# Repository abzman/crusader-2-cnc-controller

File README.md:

# crusader-2-cnc-controller
boards and roms for the crusader 2 cnc controller

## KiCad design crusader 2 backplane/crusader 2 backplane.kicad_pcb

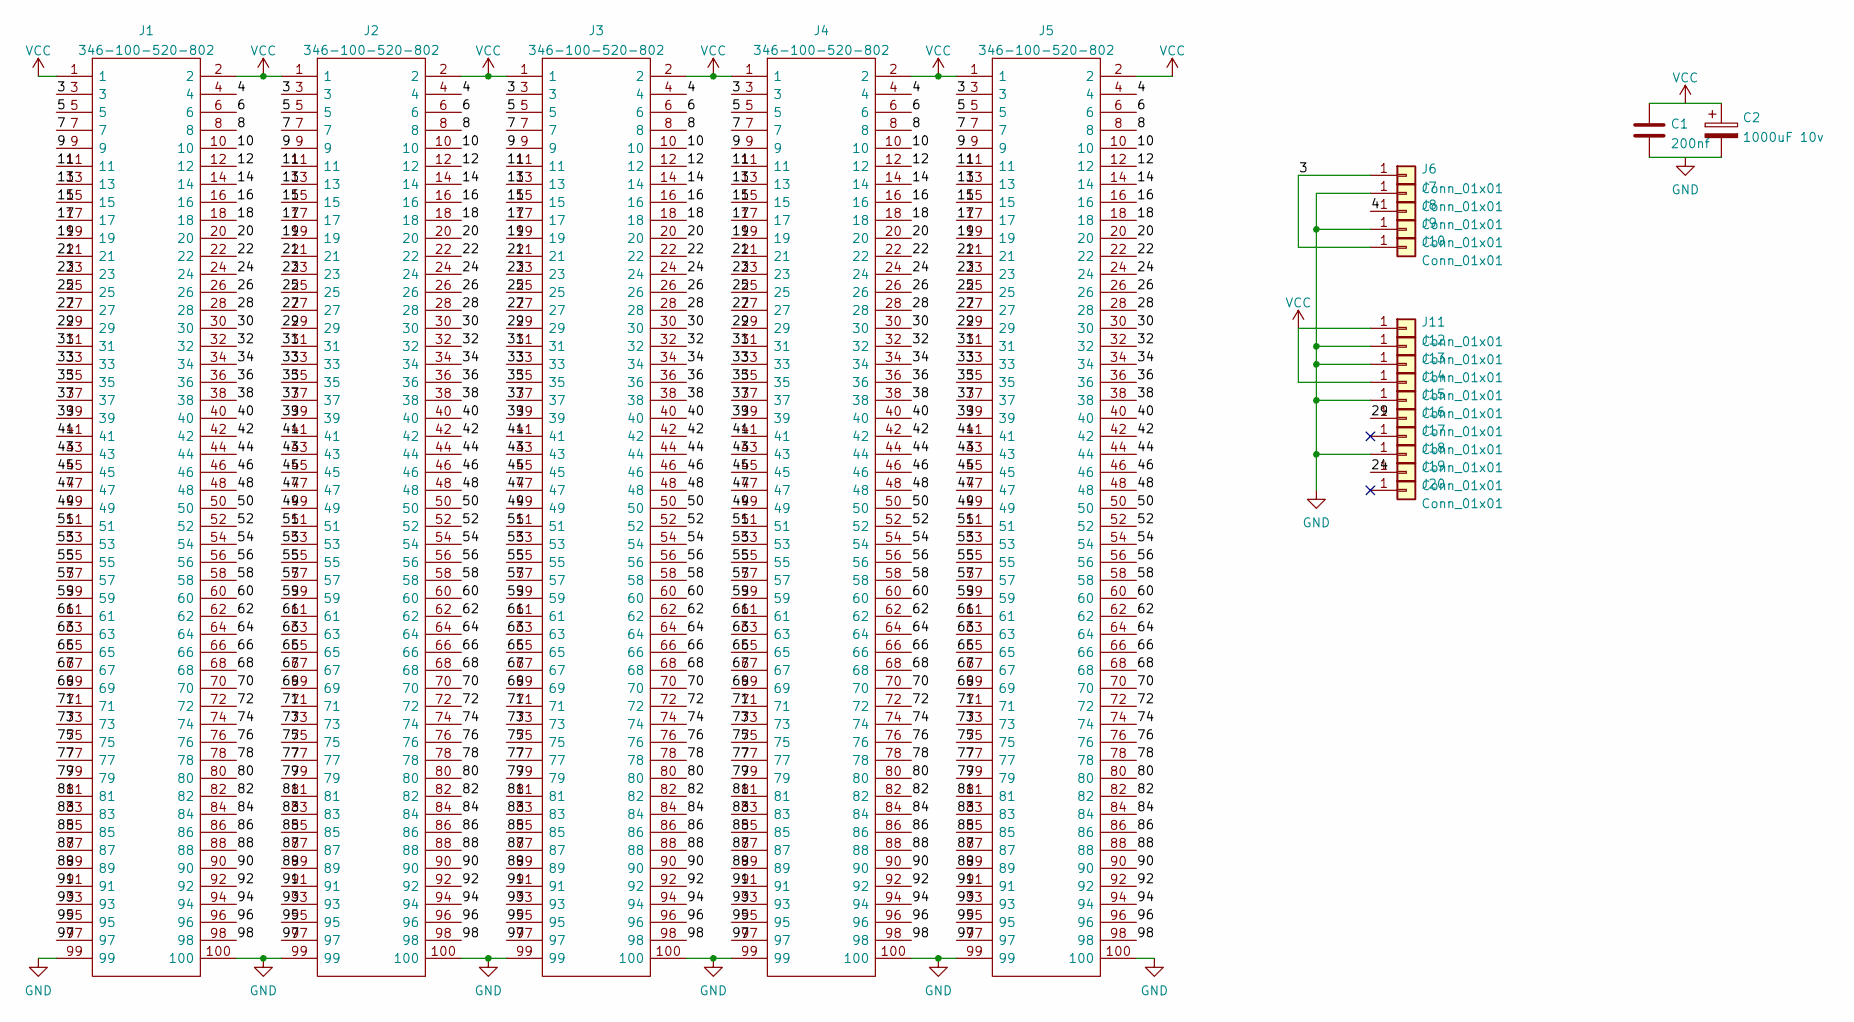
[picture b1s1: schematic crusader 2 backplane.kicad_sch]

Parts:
C1: 200nf; CP_Axial_L46.0mm_D20.0mm_P52.00mm_Horizontal
C2: 1000uF 10v; CP_Axial_L46.0mm_D20.0mm_P52.00mm_Horizontal
J1, J2, J3, J4, J5: 346-100-520-802; 346100520802; Mouser Part Number 587-346-100-520-802
J6, J7, J8, J9, J10, J11, J12, J13, J14, J15, J16, J17, J18, J19, J20: Conn_01x01; PinHeader_1x01_P2.54mm_Vertical

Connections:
/3: J1.3, J2.3, J3.3, J4.3, J5.3, J6.1, J10.1
/4: J1.4, J2.4, J3.4, J4.4, J5.4, J8.1
/5: J1.5, J2.5, J3.5, J4.5, J5.5
/6: J1.6, J2.6, J3.6, J4.6, J5.6
/7: J1.7, J2.7, J3.7, J4.7, J5.7
/8: J1.8, J2.8, J3.8, J4.8, J5.8
/9: J1.9, J2.9, J3.9, J4.9, J5.9
/10: J1.10, J2.10, J3.10, J4.10, J5.10
/11: J1.11, J2.11, J3.11, J4.11, J5.11
/12: J1.12, J2.12, J3.12, J4.12, J5.12
/13: J1.13, J2.13, J3.13, J4.13, J5.13
/14: J1.14, J2.14, J3.14, J4.14, J5.14
/15: J1.15, J2.15, J3.15, J4.15, J5.15
/16: J1.16, J2.16, J3.16, J4.16, J5.16
/17: J1.17, J2.17, J3.17, J4.17, J5.17
/18: J1.18, J2.18, J3.18, J4.18, J5.18
/19: J1.19, J2.19, J3.19, J4.19, J5.19
/20: J1.20, J2.20, J3.20, J4.20, J5.20
/21: J1.21, J2.21, J3.21, J4.21, J5.21
/22: J1.22, J2.22, J3.22, J4.22, J5.22
/23: J1.23, J2.23, J3.23, J4.23, J5.23
/24: J1.24, J2.24, J3.24, J4.24, J5.24, J19.1
/25: J1.25, J2.25, J3.25, J4.25, J5.25
/26: J1.26, J2.26, J3.26, J4.26, J5.26
/27: J1.27, J2.27, J3.27, J4.27, J5.27
/28: J1.28, J2.28, J3.28, J4.28, J5.28
/29: J1.29, J2.29, J3.29, J4.29, J5.29, J16.1
/30: J1.30, J2.30, J3.30, J4.30, J5.30
/31: J1.31, J2.31, J3.31, J4.31, J5.31
/32: J1.32, J2.32, J3.32, J4.32, J5.32
/33: J1.33, J2.33, J3.33, J4.33, J5.33
/34: J1.34, J2.34, J3.34, J4.34, J5.34
/35: J1.35, J2.35, J3.35, J4.35, J5.35
/36: J1.36, J2.36, J3.36, J4.36, J5.36
/37: J1.37, J2.37, J3.37, J4.37, J5.37
/38: J1.38, J2.38, J3.38, J4.38, J5.38
/39: J1.39, J2.39, J3.39, J4.39, J5.39
/40: J1.40, J2.40, J3.40, J4.40, J5.40
/41: J1.41, J2.41, J3.41, J4.41, J5.41
/42: J1.42, J2.42, J3.42, J4.42, J5.42
/43: J1.43, J2.43, J3.43, J4.43, J5.43
/44: J1.44, J2.44, J3.44, J4.44, J5.44
/45: J1.45, J2.45, J3.45, J4.45, J5.45
/46: J1.46, J2.46, J3.46, J4.46, J5.46
/47: J1.47, J2.47, J3.47, J4.47, J5.47
/48: J1.48, J2.48, J3.48, J4.48, J5.48
/49: J1.49, J2.49, J3.49, J4.49, J5.49
/50: J1.50, J2.50, J3.50, J4.50, J5.50
/51: J1.51, J2.51, J3.51, J4.51, J5.51
/52: J1.52, J2.52, J3.52, J4.52, J5.52
/53: J1.53, J2.53, J3.53, J4.53, J5.53
/54: J1.54, J2.54, J3.54, J4.54, J5.54
/55: J1.55, J2.55, J3.55, J4.55, J5.55
/56: J1.56, J2.56, J3.56, J4.56, J5.56
/57: J1.57, J2.57, J3.57, J4.57, J5.57
/58: J1.58, J2.58, J3.58, J4.58, J5.58
/59: J1.59, J2.59, J3.59, J4.59, J5.59
/60: J1.60, J2.60, J3.60, J4.60, J5.60
/61: J1.61, J2.61, J3.61, J4.61, J5.61
/62: J1.62, J2.62, J3.62, J4.62, J5.62
/63: J1.63, J2.63, J3.63, J4.63, J5.63
/64: J1.64, J2.64, J3.64, J4.64, J5.64
/65: J1.65, J2.65, J3.65, J4.65, J5.65
/66: J1.66, J2.66, J3.66, J4.66, J5.66
/67: J1.67, J2.67, J3.67, J4.67, J5.67
/68: J1.68, J2.68, J3.68, J4.68, J5.68
/69: J1.69, J2.69, J3.69, J4.69, J5.69
/70: J1.70, J2.70, J3.70, J4.70, J5.70
/71: J1.71, J2.71, J3.71, J4.71, J5.71
/72: J1.72, J2.72, J3.72, J4.72, J5.72
/73: J1.73, J2.73, J3.73, J4.73, J5.73
/74: J1.74, J2.74, J3.74, J4.74, J5.74
/75: J1.75, J2.75, J3.75, J4.75, J5.75
/76: J1.76, J2.76, J3.76, J4.76, J5.76
/77: J1.77, J2.77, J3.77, J4.77, J5.77
/78: J1.78, J2.78, J3.78, J4.78, J5.78
/79: J1.79, J2.79, J3.79, J4.79, J5.79
/80: J1.80, J2.80, J3.80, J4.80, J5.80
/81: J1.81, J2.81, J3.81, J4.81, J5.81
/82: J1.82, J2.82, J3.82, J4.82, J5.82
/83: J1.83, J2.83, J3.83, J4.83, J5.83
/84: J1.84, J2.84, J3.84, J4.84, J5.84
/85: J1.85, J2.85, J3.85, J4.85, J5.85
/86: J1.86, J2.86, J3.86, J4.86, J5.86
/87: J1.87, J2.87, J3.87, J4.87, J5.87
/88: J1.88, J2.88, J3.88, J4.88, J5.88
/89: J1.89, J2.89, J3.89, J4.89, J5.89
/90: J1.90, J2.90, J3.90, J4.90, J5.90
/91: J1.91, J2.91, J3.91, J4.91, J5.91
/92: J1.92, J2.92, J3.92, J4.92, J5.92
/93: J1.93, J2.93, J3.93, J4.93, J5.93
/94: J1.94, J2.94, J3.94, J4.94, J5.94
/95: J1.95, J2.95, J3.95, J4.95, J5.95
/96: J1.96, J2.96, J3.96, J4.96, J5.96
/97: J1.97, J2.97, J3.97, J4.97, J5.97
/98: J1.98, J2.98, J3.98, J4.98, J5.98

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
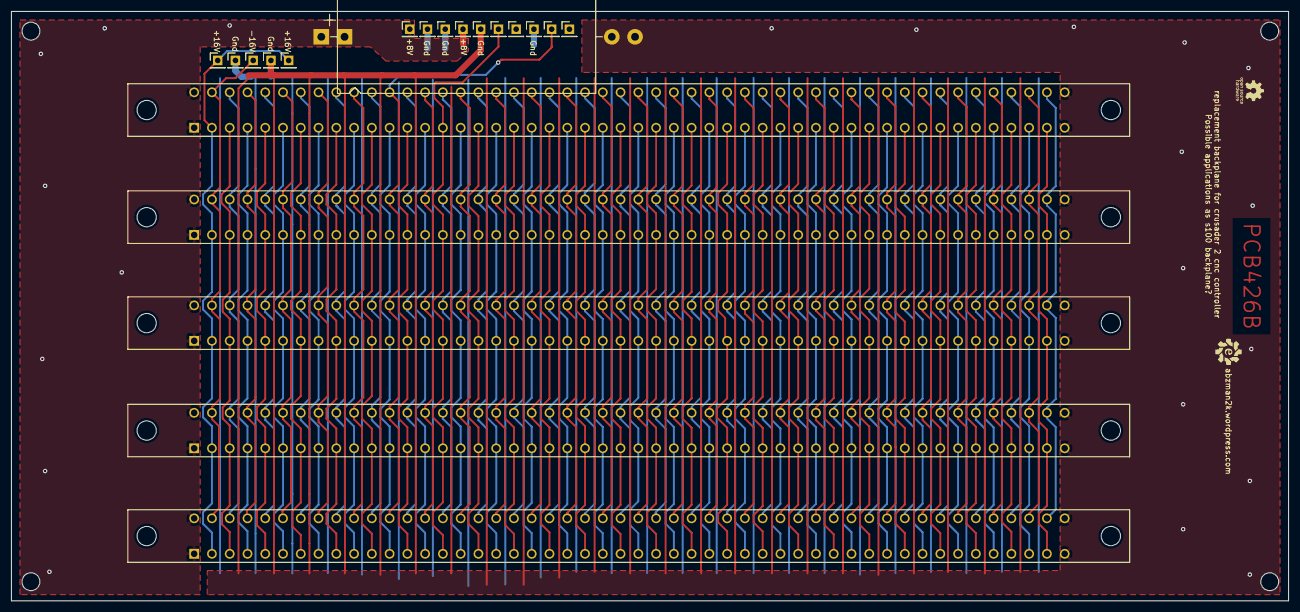
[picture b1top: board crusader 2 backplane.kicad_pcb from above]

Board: 2 copper layers, 228.6 x 105.5 mm, 22 parts (1 on the bottom side), 100 nets.

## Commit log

2022-01-25 added rom dumps and backplane board
2022-11-25 added gitignore
2024-04-08 added some roms from ebay
